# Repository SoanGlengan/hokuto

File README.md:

# small project to build a stream deck esque thing

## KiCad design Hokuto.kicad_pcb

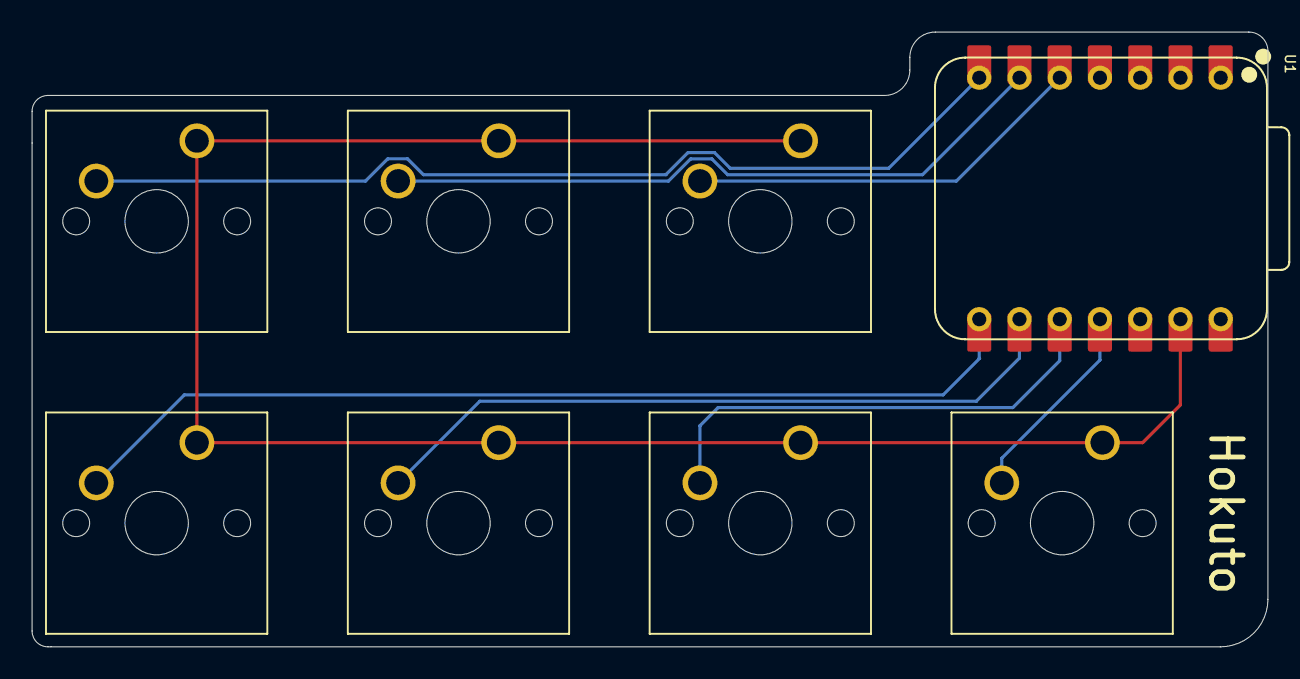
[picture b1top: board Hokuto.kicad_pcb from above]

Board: 2 copper layers, 78.0 x 38.8 mm, 8 parts (0 on the bottom side), 8 nets.

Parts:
SW1, SW2, SW3, SW4, SW5, SW6, SW7: SW_Push; SW_Cherry_MX_1.00u_PCB
U1: XIAO-RP2040-DIP

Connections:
GND: SW1.1, SW2.1, SW3.1, SW4.1, SW5.1, SW6.1, SW7.1, U1.13 (GND)
SW1: SW1.2, U1.7 (GPIO0/TX)
SW2: SW2.2, U1.8 (GPIO1/RX)
SW3: SW3.2, U1.6 (GPIO7/SCL)
SW4: SW4.2, U1.9 (GPIO2/SCK)
SW5: SW5.2, U1.5 (GPIO6/SDA)
SW6: SW6.2, U1.10 (GPIO4/MISO)
SW7: SW7.2, U1.11 (GPIO3/MOSI)

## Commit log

2025-11-21 add kicad files
2025-11-21 pcb mostly finished
2025-11-21 i forgot to save the file so it didnt commit :(
